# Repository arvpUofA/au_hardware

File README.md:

# au_hardware #

Welcome to ARVP's hardware design repository.

In here you can find all of our electrical designs.

### Github Guides
- http://rogerdudler.github.io/git-guide/ 
- Intro to GitHub with Hello World
- https://www.youtube.com/watch?v=0fKg7e37bQE 

## Branches
- master -  contains boards that have been fabricated, soldered, tested and are part of this year’s robot
- develop - contains boards that have been designed, approved, and the fab company has accepted their designs.
- project_branch - every new project is branched from develop. Naming convention of branch is as follows:

All names in lowercase and can only include alphanumeric characters and underscores.
The naming format will be `project_board` (e.g. `motor_breakout` or `power_main`)
If the project only contains one board (e.g. `killswitch`) then naming format will be `project`.
If this is a newer iteration of the same board create a branch with the version number `project_board_vx` (where `x` is the version number).

## Starting a new project

```
    # Clone the develop branch of the repository
    git clone -b develop https://github.com/arvpUofA/au_hardware 
    # Create a new branch from develop
    git checkout -b project_board   
    # Push the branch to remote
    git push -u origin project_board
```

Create folder structure for project as follows:
Inside the `au_hardware`/`project_board` branch, create the project folder if it does not exist. (e.g. `motor`, `power`, etc)
Inside the project folder create a board folder if it does not exist. If this is a different version of the same board, don’t create a new folder. Use the same folder as before. If the project contains only one board, you don’t need to create this folder.
Naming of the folder will follow the same conventions as branch naming conventions (no spaces please). 
Add required files to this folder. Make sure to commit and push periodically.

## Project requirements
Once the board design is complete, run the following:

- ERC on schematic - error checking for schematic
- DRC on board - design rule check for pcb. (e.g. drc/JLCPCB2Layer.drc file)
- Generate image files for schematic and pcb. Make sure the images are clear with at least 200dpi.
- Generate CAM files.
- Test CAM files using a CAM Viewer (e.g. View Mate or Gerbv)

Each project needs the following files:
- [ ] project_board.sch - schematic file for project
- [ ] project_board.brd - board file for project
- [ ] project_board_sch.png - image of schematic
- [ ] project_board_brd.png - image of pcb
- [ ] project_board/ - this folder contains all the CAM files
- [ ] project_board.zip - ZIP of the CAM folder

## Pull request and close

Once all requirements have been complete, create a pull request to merge this branch into develop

Set base: `develop` and compare: `your_branch`. Click "Create pull request".
 
Set the PR name, create a detailed description, and assign the team lead to review your pull request.   
The reviewer will check your design, and rerun ERC and DRC.

If the reviewer has any suggestions, implement them in your design, regenerate all required files and commit and push everything.

After the review is complete, the board will be uploaded to the fabrication website. If they approve the design, the reviewer will merge and close the pull request. Make sure you don’t continue work on this closed branch.
A new release tag will also be created for the board with format boardname[version]. E.g. killswitch1.0. At any point you can look at any older version by going to that specific tag.
Note that, if during reviews we discovered any changes we want to make in the next version, we will put these as issues on the repository and assign them to you. These need to be fixed in the next version before you make a PR.

## Starting a new revision

Once your PRs have been closed a.k.a the board has been sent out, the branch you were working on will be deleted, and you will need to make
a new branch off `develop` with the latest version number for that board.

```
    # To start switch to develop
    git checkout develop
    # Pull the latest version of the code
    git pull 
```

Create a new branch for the next iteration of the board. The naming format for the branch is `boardname_vx`

```
    # Example for V2 of comm_hub
    git checkout -b comm_hub_v2
```

Find the appropriate project folder where the current board revision is saved (e.g.  communications_hub) and create a new folder within this project folder with the new version number (e.g. communications_hub\communications_hub_v2).
Make sure to push your new branch to github using 

```
git push -u origin name_of_new_branch
```

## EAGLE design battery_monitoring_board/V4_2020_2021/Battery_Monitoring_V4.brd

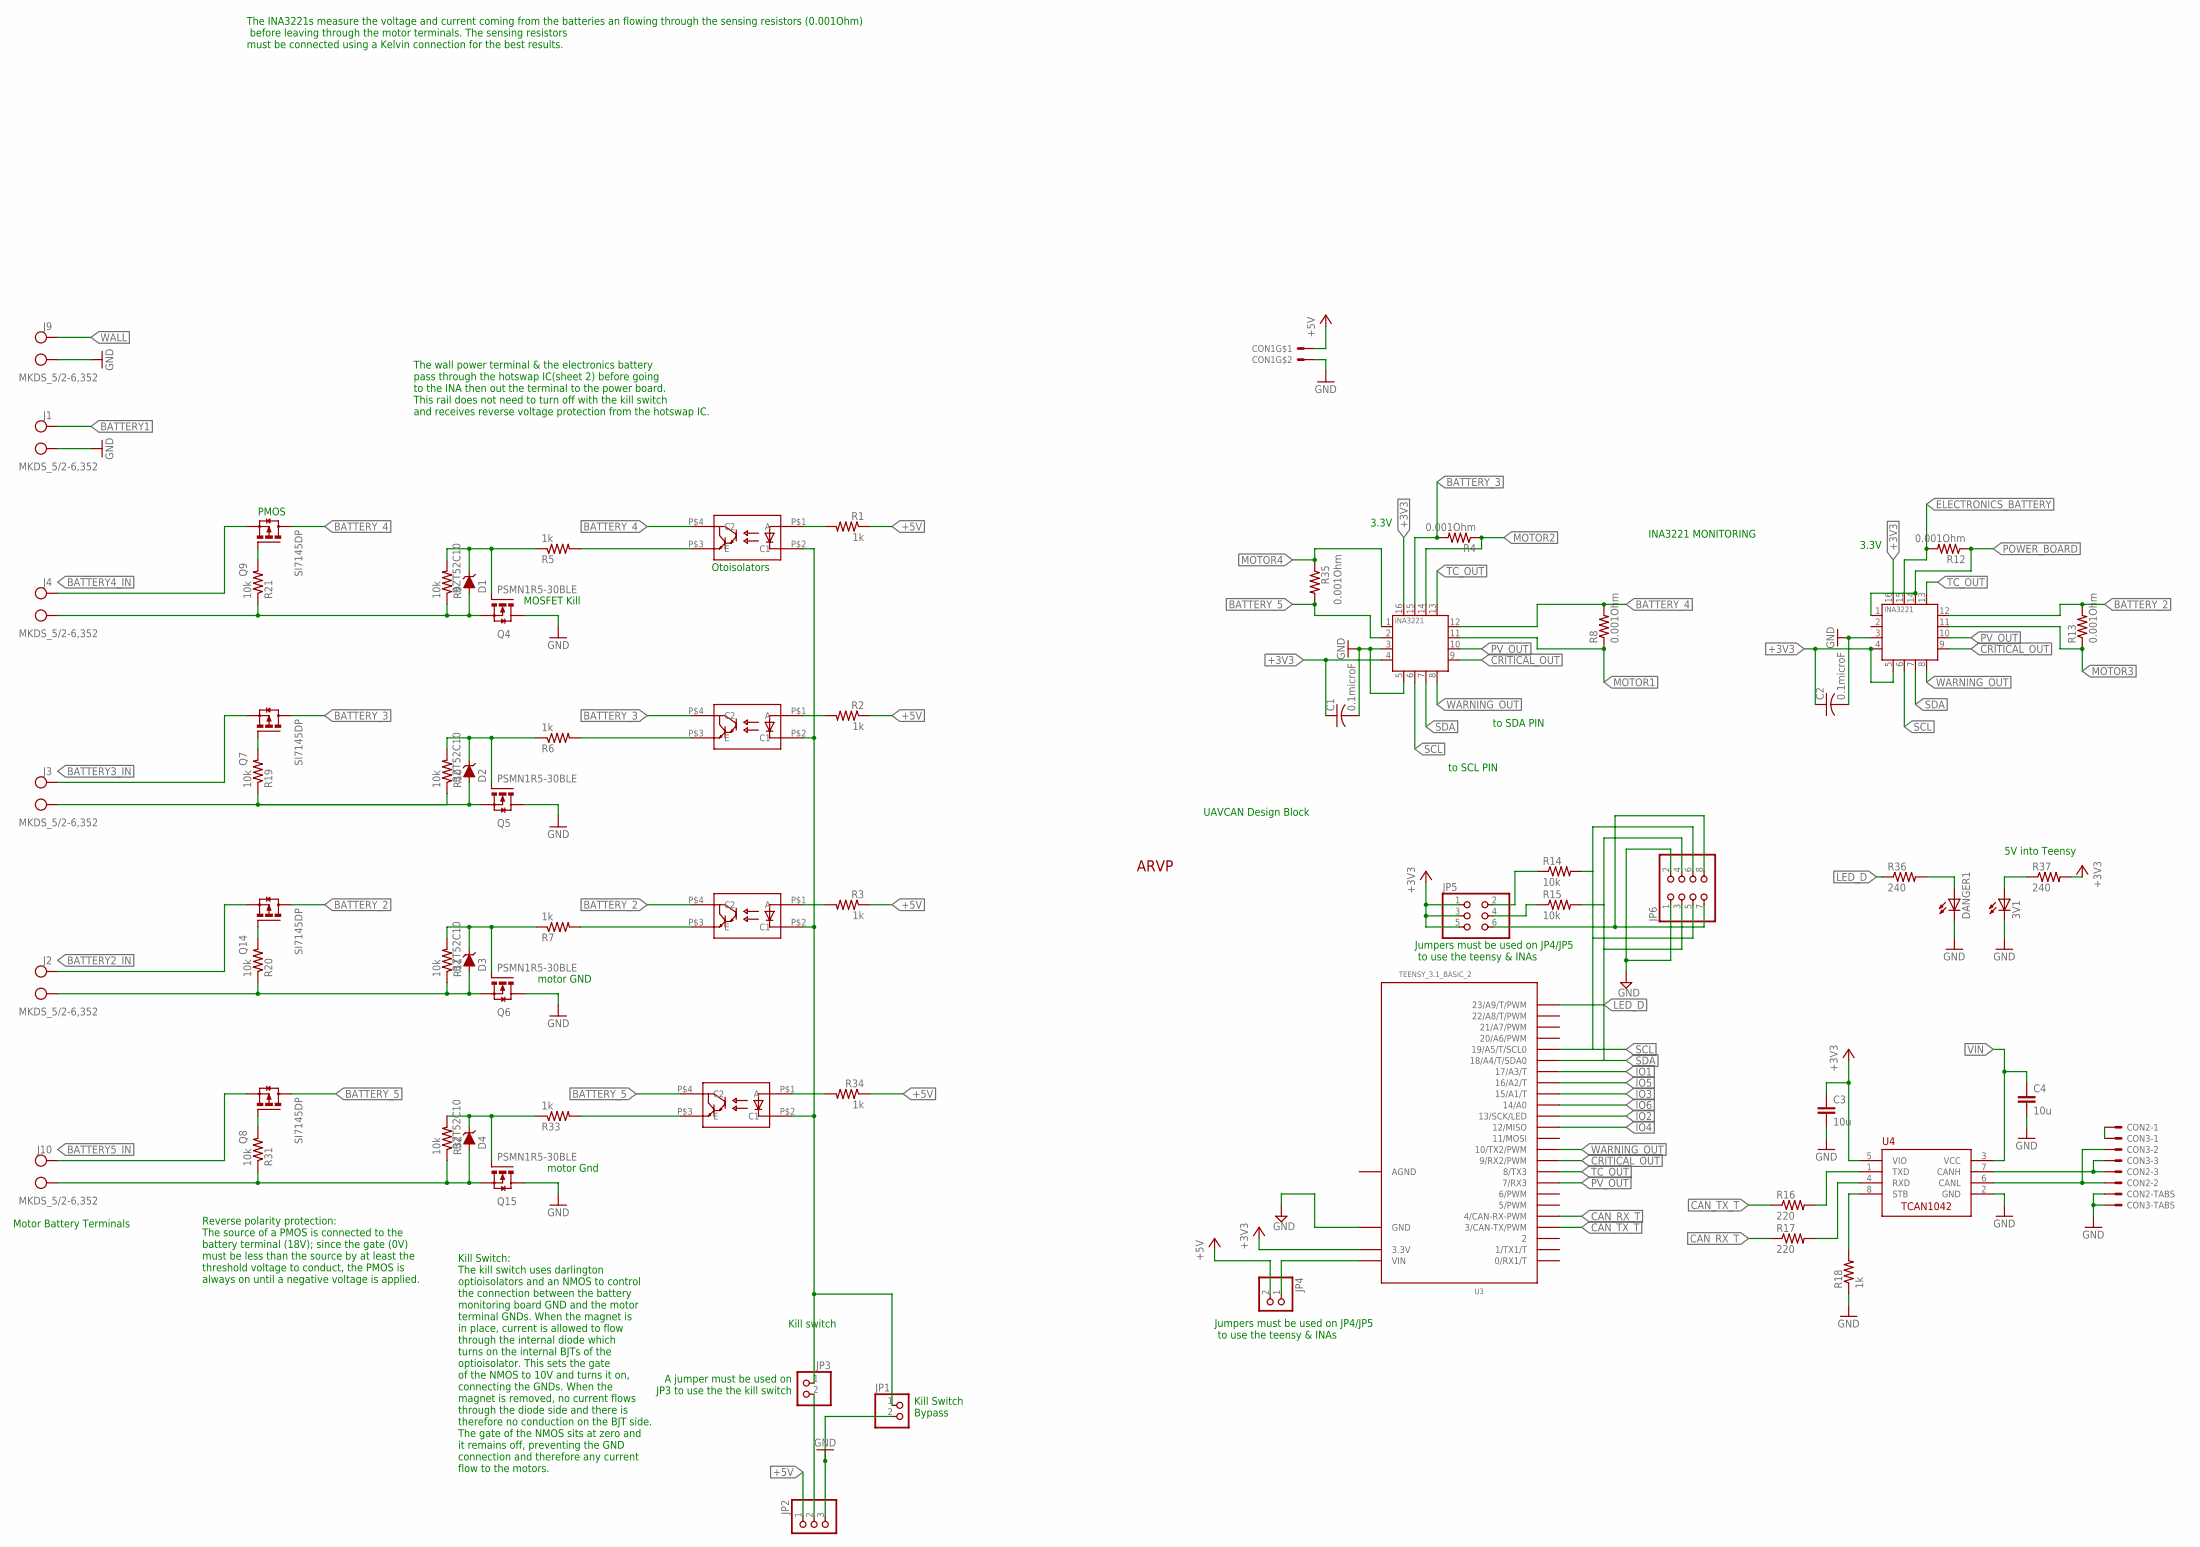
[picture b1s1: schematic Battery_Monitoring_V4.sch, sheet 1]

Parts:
3V1: LEDSMT1206; 1206
ARVP1: ARVP_LOGO; ARVP
C1, C2: 0.1microF; C2012
C3, C4: 10u; C0805
CON1: MOLEX_5566-2; 5566-2
CON2, CON3: SM03B-GHS-TB
D1, D2, D3, D4: BZT52C10; SOD-123
DANGER1: LEDSMT1206; 1206
J1, J2, J3, J4, J9, J10: MKDS_5/2-6,352; MKDS_5/2-6,35
JP1, JP3, JP4: PINHD-1X2; 1X02
JP2: PINHD-1X3; 1X03
JP5: PINHD-2X3; 2X03
JP6: PINHD-2X4; 2X04
Q1, Q2, Q3, Q16: TCLD1000CT; SOP-4L
Q4, Q5, Q6, Q15: PSMN1R5-30BLE; SOT404/D2PAK
Q7, Q8, Q9, Q14: SI7145DP; SO-8/PPAK/TEST; MPN SI7145DP-T1-GE3
R1, R2, R3, R18, R34: 1k; R0805
R4, R8, R12, R13, R35: 0.001Ohm; 3920
R5, R6, R7, R33: 1k; M1206
R9, R10, R11, R32: 10k; M1206
R14, R15: 10k; R1206
R16, R17: 220; R0805
R19, R20, R21, R31: 10k; M1206; MPN RC0603FR-0710KL
R36, R37: 240; R1206
U1, U2: INA3221.; HVQFN16_4X4
U3: TEENSY_3.1_BASIC_2
U4: TCAN1042HVDR; SO-8

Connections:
+3V3: C1.1, C2.1, C3.1, JP5.1, JP5.3, JP5.5, R37.2, U1.4 (VS), U1.16 (VPU), U2.4 (VS), U2.5 (A0), U2.16 (VPU), U3.3.3V, U4.5 (VIO)
+5V: CON1.1, JP2.1, JP4.2, R1.1, R2.1, R3.1, R34.1; also elsewhere on the board
AGND: U3.AGND
BATT1GND: D1.P$2 (A), J4.1 (KL), Q4.3S (S), R9.1, R21.1
BATT2GND: D2.P$2 (A), J3.1 (KL), Q5.3S (S), R10.1, R19.1
BATT3GND: D3.P$2 (A), J2.1 (KL), Q6.3S (S), R11.1, R20.1
BATT5GND: D4.P$2 (A), J10.1 (KL), Q15.3S (S), R31.1, R32.1
BATTERY1: J1.2 (KL1); also elsewhere on the board
BATTERY2_IN: J2.2 (KL1), Q14.S@1 (S), Q14.S@2 (S), Q14.S@3 (S)
BATTERY3_IN: J3.2 (KL1), Q7.S@1 (S), Q7.S@2 (S), Q7.S@3 (S)
BATTERY4_IN: J4.2 (KL1), Q9.S@1 (S), Q9.S@2 (S), Q9.S@3 (S)
BATTERY5_IN: J10.2 (KL1), Q8.S@1 (S), Q8.S@2 (S), Q8.S@3 (S)
BATTERY_2: Q3.P$4 (C2), Q14.D@1 (D), Q14.D@2 (D), Q14.D@3 (D), Q14.D@4 (D), Q14.D@5 (D), R13.P$2 (2), U2.12 (IN+1)
BATTERY_3: Q2.P$4 (C2), Q7.D@1 (D), Q7.D@2 (D), Q7.D@3 (D), Q7.D@4 (D), Q7.D@5 (D), R4.P$2 (2), U1.15 (IN+2)
BATTERY_4: Q1.P$4 (C2), Q9.D@1 (D), Q9.D@2 (D), Q9.D@3 (D), Q9.D@4 (D), Q9.D@5 (D), R8.P$2 (2), U1.12 (IN+1)
BATTERY_5: Q8.D@1 (D), Q8.D@2 (D), Q8.D@3 (D), Q8.D@4 (D), Q8.D@5 (D), Q16.P$4 (C2), R35.P$2 (2), U1.2 (IN+3)
CANH1: CON2.P$3, CON3.P$3, U4.7 (CANH)
CANL1: CON2.P$2, CON3.P$2, U4.6 (CANL)
CANSH1: CON2.P$1, CON3.P$1
CAN_RX1: R17.2, U4.4 (RXD)
CAN_RX_T: R17.1, U3.4 (4/CAN-RX-PWM)
CAN_TX2: R16.2, U4.1 (TXD)
CAN_TX_T: R16.1, U3.3 (3/CAN-TX/PWM)
CRITICAL_OUT: U1.9 (CRITICAL), U2.9 (CRITICAL), U3.9 (9/RX2/PWM)
E1: Q1.P$3 (E), R5.2
E2: Q2.P$3 (E), R6.2
E3: Q3.P$3 (E), R7.2
ELECTRONICS_BATTERY: R12.P$2 (2), U2.15 (IN+2); also elsewhere on the board
GND: 3V1.C, C1.2, C2.2, C3.2, C4.2, CON1.2, CON2.P$4, CON2.P$5, CON3.P$4, CON3.P$5, DANGER1.C, J1.1 (KL), J9.1 (KL), JP1.2, JP2.3, JP6.1, JP6.2, Q4.2D (D), Q5.2D (D), Q6.2D (D), Q15.2D (D), R18.1, U1.3 (GND), U1.5 (A0), U2.3 (GND), U3.GND, U4.2 (GND); also elsewhere on the board
I2C_3V1: JP5.6, JP6.7, JP6.8
IO1: U3.17/A3 (17/A3/T); also elsewhere on the board
IO2: U3.13 (13/SCK/LED); also elsewhere on the board
IO3: U3.15/A1 (15/A1/T); also elsewhere on the board
IO4: U3.12 (12/MISO); also elsewhere on the board
IO5: U3.16/A2 (16/A2/T); also elsewhere on the board
IO6: U3.14/A0; also elsewhere on the board
LED_D: R36.1, U3.23/A9 (23/A9/T/PWM)
MG1: D1.P$1 (C), Q4.1G (G), R5.1, R9.2
MG2: D2.P$1 (C), Q5.1G (G), R6.1, R10.2
MG3: D3.P$1 (C), Q6.1G (G), R7.1, R11.2
MG4: D4.P$1 (C), Q15.1G (G), R32.2, R33.1
MOTOR1: R8.P$1 (1), U1.11 (IN-1); also elsewhere on the board
MOTOR2: R4.P$1 (1), U1.14 (IN-2); also elsewhere on the board
MOTOR3: R13.P$1 (1), U2.11 (IN-1); also elsewhere on the board
MOTOR4: R35.P$1 (1), U1.1 (IN-3); also elsewhere on the board
unnamed: Q1.P$1 (A), R1.2
unnamed: Q2.P$1 (A), R2.2
unnamed: Q3.P$1 (A), R3.2
unnamed: JP1.1, JP3.1, Q1.P$2 (C1), Q2.P$2 (C1), Q3.P$2 (C1), Q16.P$2 (C1)
unnamed: JP2.2, JP3.2
unnamed: Q7.G, R19.2
unnamed: Q14.G, R20.2
unnamed: Q9.G, R21.2
unnamed: Q8.G, R31.2
unnamed: Q16.P$3 (E), R33.2
unnamed: Q16.P$1 (A), R34.2
unnamed: 3V1.A, R37.1
unnamed: DANGER1.A, R36.2
POWER_BOARD: R12.P$1 (1), U2.1 (IN-3), U2.14 (IN-2); also elsewhere on the board
PV_OUT: U1.10 (PV), U2.10 (PV), U3.7 (7/RX3)
SCL: JP6.5, JP6.6, R14.2, U1.6 (SCL), U2.6 (SCL), U3.19/A5 (19/A5/T/SCL0)
SCL_3V1: JP5.2, R14.1
SDA: JP6.3, JP6.4, R15.2, U1.7 (SDA), U2.7 (SDA), U3.18/A4 (18/A4/T/SDA0)
SDA_3V1: JP5.4, R15.1
STB1: R18.2, U4.8 (STB)
TC_OUT: U1.13 (TC), U2.13 (TC), U3.8 (8/TX3)
VIN: C4.1, JP4.1, U3.VIN, U4.3 (VCC)
WALL: J9.2 (KL1); also elsewhere on the board
WARNING_OUT: U1.8 (WARNING), U2.8 (WARNING), U3.10 (10/TX2/PWM)

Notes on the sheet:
3.3V
Kill switch
motor GND
INA3221 MONITORING
Otoisolators
MOSFET Kill
to SDA PIN
to SCL PIN
A jumper must be used on JP3 to use the the kill switch
Kill Switch Bypass
PMOS
The wall power terminal & the electronics battery pass through the hotswap IC(sheet 2) before going to the INA then out the terminal to the power board. This rail does not need to turn off with the kill switch and receives reverse voltage protection from the hotswap IC.
The INA3221s measure the voltage and current coming from the batteries an flowing through the sensing resistors (0.001Ohm) before leaving through the motor terminals. The sensing resistors must be connected using a Kelvin connection for the best results.
Jumpers must be used on JP4/JP5 to use the teensy & INAs
Reverse polarity protection: The source of a PMOS is connected to the battery terminal (18V); since the gate (0V) must be less than the source by at least the threshold voltage to conduct, the PMOS is always on until a negative voltage is applied.
Kill Switch: The kill switch uses darlington optioisolators and an NMOS to control the connection between the battery monitoring board GND and the motor terminal GNDs. When the magnet is in place, current is allowed to flow through the internal diode which turns on the internal BJTs of the optioiso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
UAVCAN Design Block
Motor Battery Terminals
motor Gnd
5V into Teensy

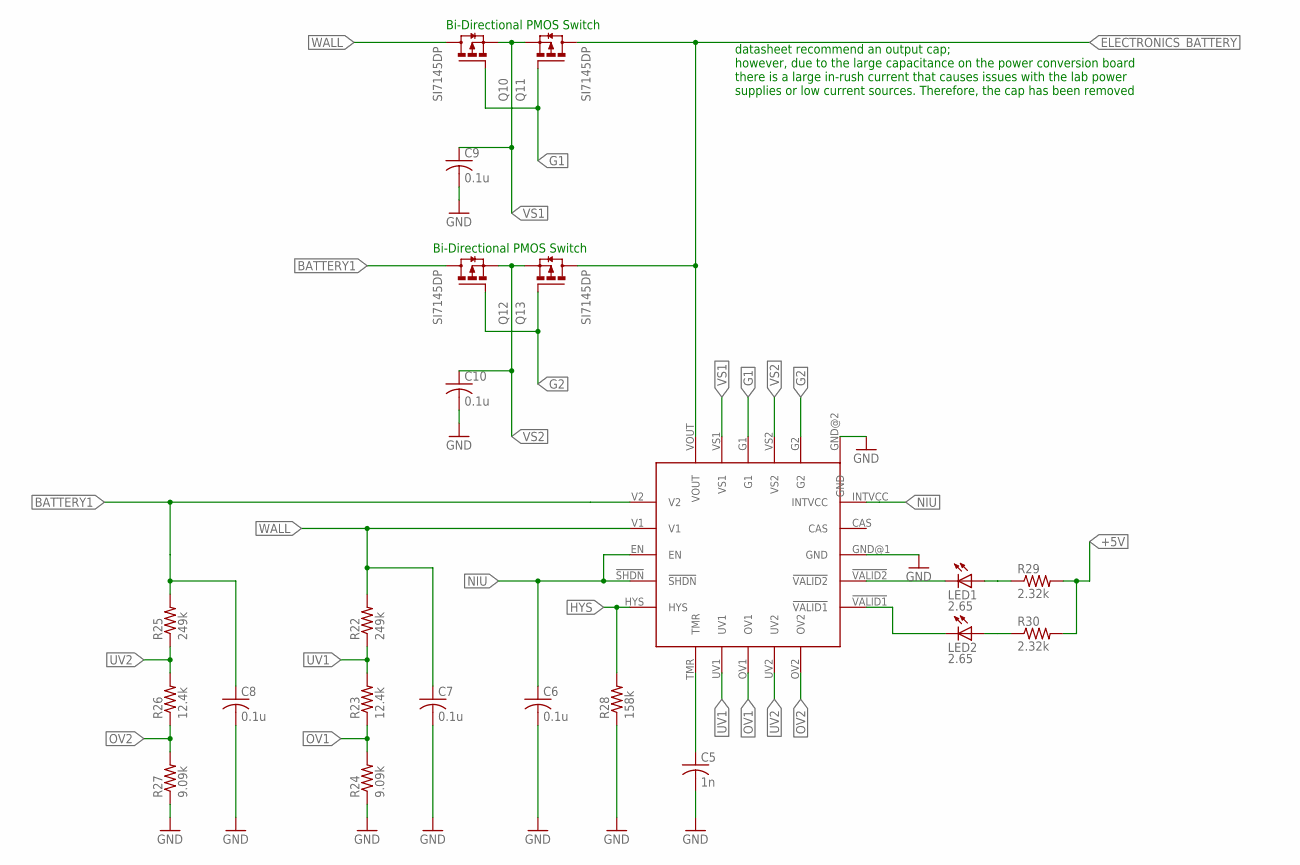
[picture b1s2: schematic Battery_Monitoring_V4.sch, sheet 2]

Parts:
C5: 1n; C0805
C6, C7, C8, C9, C10: 0.1u; C0805
LED1, LED2: 2.65; SML0805
Q10, Q11, Q12, Q13: SI7145DP; SO-8/PPAK/TEST
R22, R25: 249k; R1206
R23, R26: 12.4k; R0805
R24, R27: 9.09k; R0805
R28: 158k; R0805
R29, R30: 2.32k; R0805
U5: LTC4418; 20-QFN(4X4)

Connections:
!VALID1: LED2.C, U5.!VALID1
!VALID2: LED1.C, U5.!VALID2
+5V: R29.2, R30.2; also elsewhere on the board
BATTERY1: C8.1, Q12.D@1 (D), Q12.D@2 (D), Q12.D@3 (D), Q12.D@4 (D), Q12.D@5 (D), R25.2, U5.V2; also elsewhere on the board
ELECTRONICS_BATTERY: Q11.D@1 (D), Q11.D@2 (D), Q11.D@3 (D), Q11.D@4 (D), Q11.D@5 (D), Q13.D@1 (D), Q13.D@2 (D), Q13.D@3 (D), Q13.D@4 (D), Q13.D@5 (D), U5.VOUT; also elsewhere on the board
G1: Q10.G, Q11.G, U5.G1
G2: Q12.G, Q13.G, U5.G2
GND: C5.2, C6.2, C7.2, C8.2, C9.2, C10.2, R24.1, R27.1, R28.1, U5.GND@1 (GND), U5.GND@2 (GND); also elsewhere on the board
HYS: R28.2, U5.HYS
unnamed: LED1.A, R29.1
unnamed: LED2.A, R30.1
unnamed: C5.1, U5.TMR
NIU: C6.1, U5.!SHDN, U5.EN, U5.INTVCC
OV1: R23.1, R24.2, U5.OV1
OV2: R26.1, R27.2, U5.OV2
UV1: R22.1, R23.2, U5.UV1
UV2: R25.1, R26.2, U5.UV2
VS1: C9.1, Q10.S@1 (S), Q10.S@2 (S), Q10.S@3 (S), Q11.S@1 (S), Q11.S@2 (S), Q11.S@3 (S), U5.VS1
VS2: C10.1, Q12.S@1 (S), Q12.S@2 (S), Q12.S@3 (S), Q13.S@1 (S), Q13.S@2 (S), Q13.S@3 (S), U5.VS2
WALL: C7.1, Q10.D@1 (D), Q10.D@2 (D), Q10.D@3 (D), Q10.D@4 (D), Q10.D@5 (D), R22.2, U5.V1; also elsewhere on the board

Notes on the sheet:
Bi-Directional PMOS Switch
datasheet recommend an output cap; however, due to the large capacitance on the power conversion board there is a large in-rush current that causes issues with the lab power supplies or low current sources. Therefore, the cap has been removed

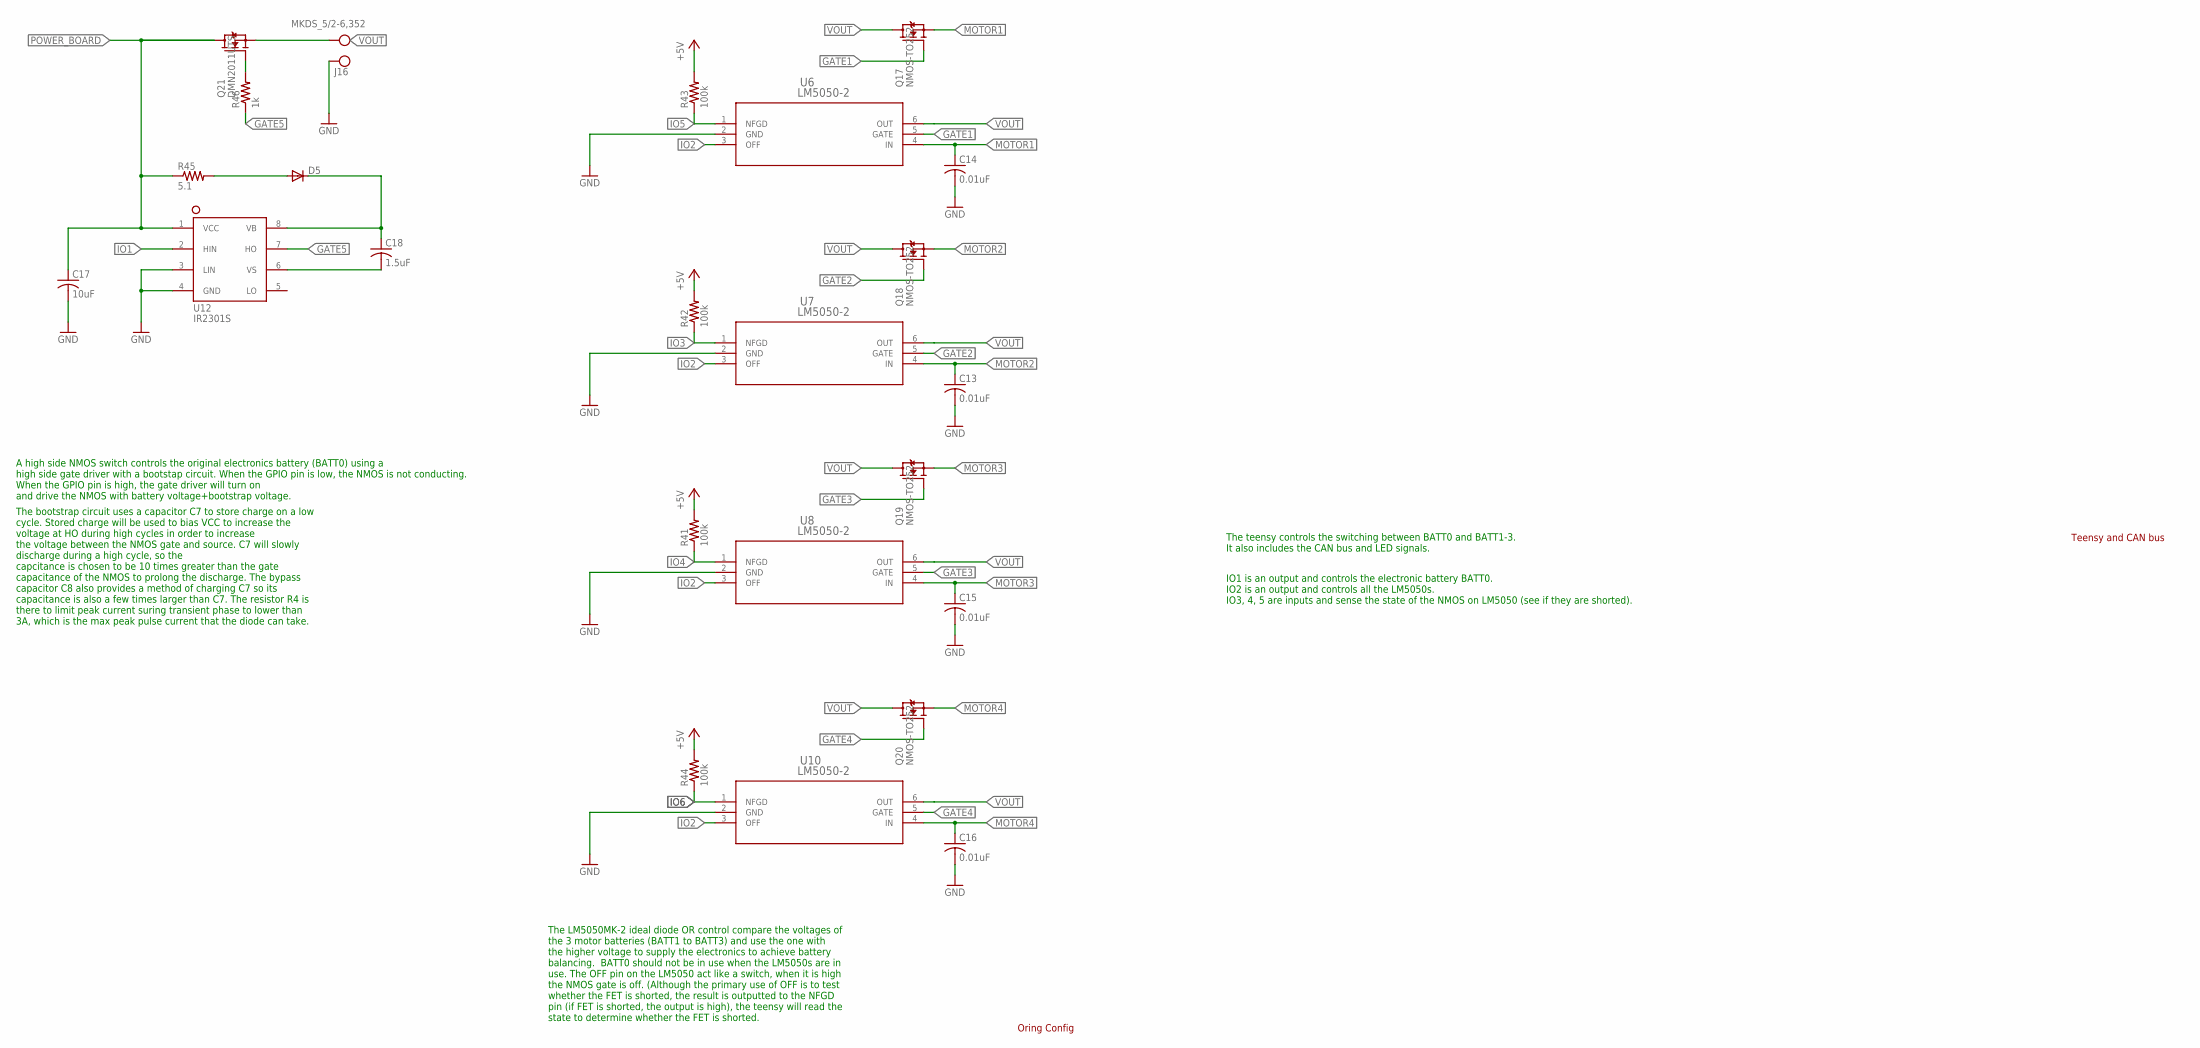
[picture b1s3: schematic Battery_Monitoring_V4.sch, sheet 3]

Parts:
C13, C14, C15, C16: 0.01uF; C0805
C17: 10uF; C1206
C18: 1.5uF; C0805
D5: DIODE-DO-214AC; DO-214AC
J16: MKDS_5/2-6,352; MKDS_5/2-6,35
Q17, Q18, Q19, Q20: NMOS-TO252; TO252
Q21: DMN2011UTS; SOP65P640X120-8N
R41, R42, R43, R44: 100k; R1206
R45: 5.1; R1206
R46: 1k; R0805
U6, U7, U8, U10: LM5050-2; MK06A
U12: IR2301S; SOIC8

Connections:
+5V: R41.2, R42.2, R43.2, R44.2; also elsewhere on the board
GATE1: Q17.1 (G), U6.5 (GATE)
GATE2: Q18.1 (G), U7.5 (GATE)
GATE3: Q19.1 (G), U8.5 (GATE)
GATE4: Q20.1 (G), U10.5 (GATE)
GATE5: R46.1, U12.7 (HO)
GND: C13.2, C14.2, C15.2, C16.2, C17.2, J16.2 (KL1), U6.2 (GND), U7.2 (GND), U8.2 (GND), U10.2 (GND), U12.3 (LIN), U12.4 (GND); also elsewhere on the board
IO1: U12.2 (HIN); also elsewhere on the board
IO2: U6.3 (OFF), U7.3 (OFF), U8.3 (OFF), U10.3 (OFF); also elsewhere on the board
IO3: R42.1, U7.1 (NFGD); also elsewhere on the board
IO4: R41.1, U8.1 (NFGD); also elsewhere on the board
IO5: R43.1, U6.1 (NFGD); also elsewhere on the board
IO6: R44.1, U10.1 (NFGD); also elsewhere on the board
MOTOR1: C14.1, Q17.3 (S), U6.4 (IN); also elsewhere on the board
MOTOR2: C13.1, Q18.3 (S), U7.4 (IN); also elsewhere on the board
MOTOR3: C15.1, Q19.3 (S), U8.4 (IN); also elsewhere on the board
MOTOR4: C16.1, Q20.3 (S), U10.4 (IN); also elsewhere on the board
unnamed: C18.2, U12.6 (VS)
unnamed: C18.1, D5.C, U12.8 (VB)
unnamed: Q21.4 (G), R46.2
unnamed: D5.A, R45.2
POWER_BOARD: C17.1, Q21.5 (D), Q21.6 (D), Q21.7 (D), Q21.8 (D), R45.1, U12.1 (VCC); also elsewhere on the board
VOUT: J16.1 (KL), Q17.2 (D), Q18.2 (D), Q19.2 (D), Q20.2 (D), Q21.1 (S), Q21.2 (S), Q21.3 (S), U6.6 (OUT), U7.6 (OUT), U8.6 (OUT), U10.6 (OUT)

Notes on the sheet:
Teensy and CAN bus
Oring Config
A high side NMOS switch controls the original electronics battery (BATT0) using a high side gate driver with a bootstap circuit. When the GPIO pin is low, the NMOS is not conducting. When the GPIO pin is high, the gate driver will turn on and drive the NMOS with battery voltage+bootstrap voltage.
The LM5050MK-2 ideal diode OR control compare the voltages of the 3 motor batteries (BATT1 to BATT3) and use the one with the higher voltage to supply the electronics to achieve battery balancing. BATT0 should not be in use when the LM5050s are in use. The OFF pin on the LM5050 act like a switch, w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
The teensy controls the switching between BATT0 and BATT1-3. It also includes the CAN bus and LED signals.
IO1 is an output and controls the electronic battery BATT0. IO2 is an output and controls all the LM5050s. IO3, 4, 5 are inputs and sense the state of the NMOS on LM5050 (see if they are shorted).
The bootstrap circuit uses a capacitor C7 to store charge on a low cycle. Stored charge will be used to bias VCC to increase the voltage at HO during high cycles in order to increase the voltage between the NMOS gate and source. C7 will slowly discharge during a high cycle, so the capcitance is cho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

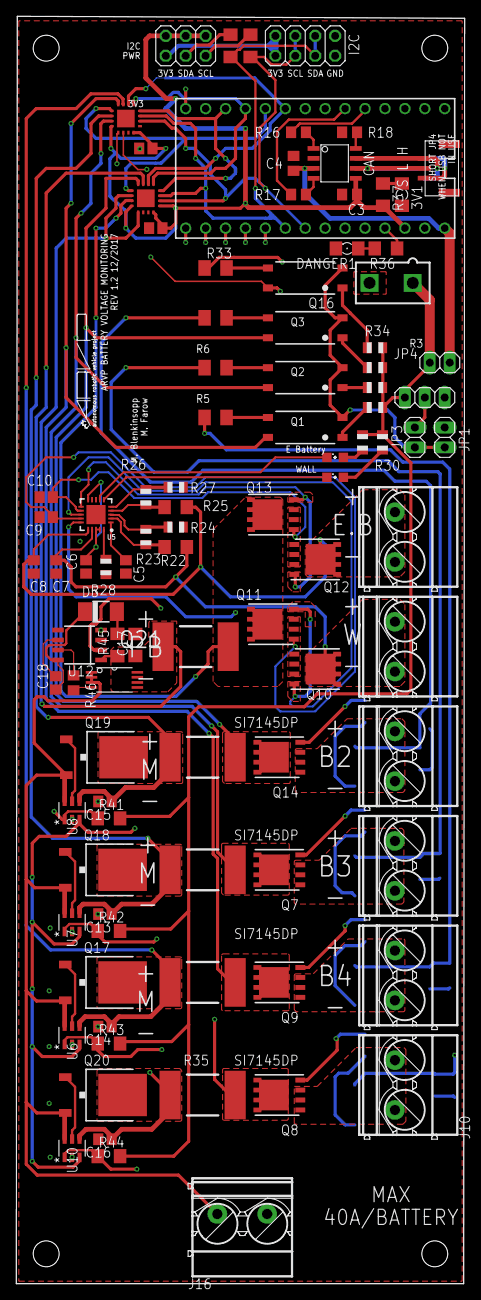
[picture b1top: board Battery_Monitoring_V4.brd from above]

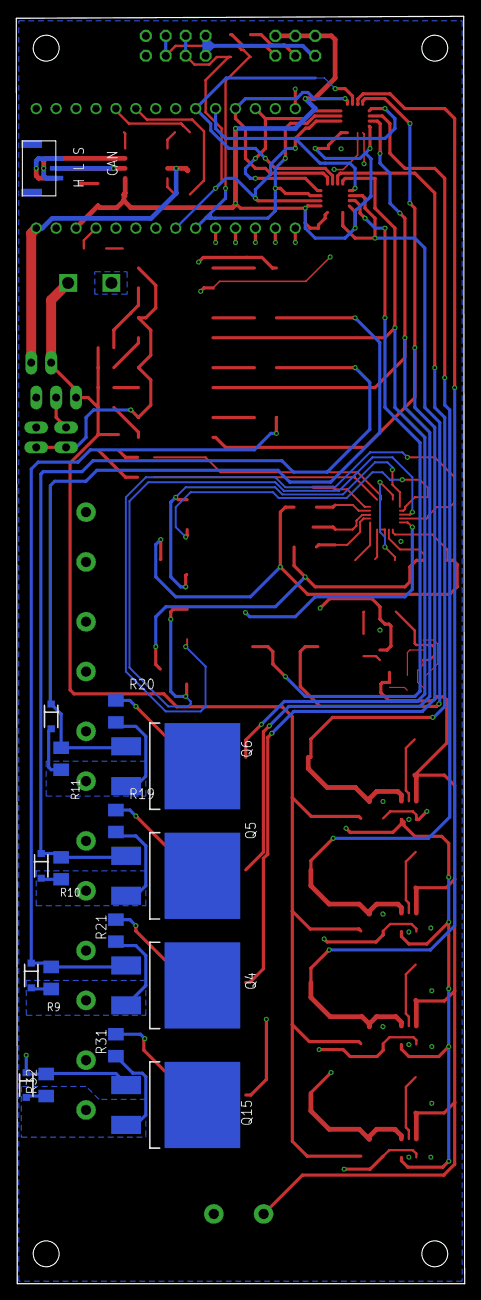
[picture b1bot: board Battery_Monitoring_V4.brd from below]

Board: 4 copper layers, 57.1 x 161.5 mm, 120 parts (17 on the bottom side), 93 nets.

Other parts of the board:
U$18, U$24, U$25, U$26: STAND-OFF

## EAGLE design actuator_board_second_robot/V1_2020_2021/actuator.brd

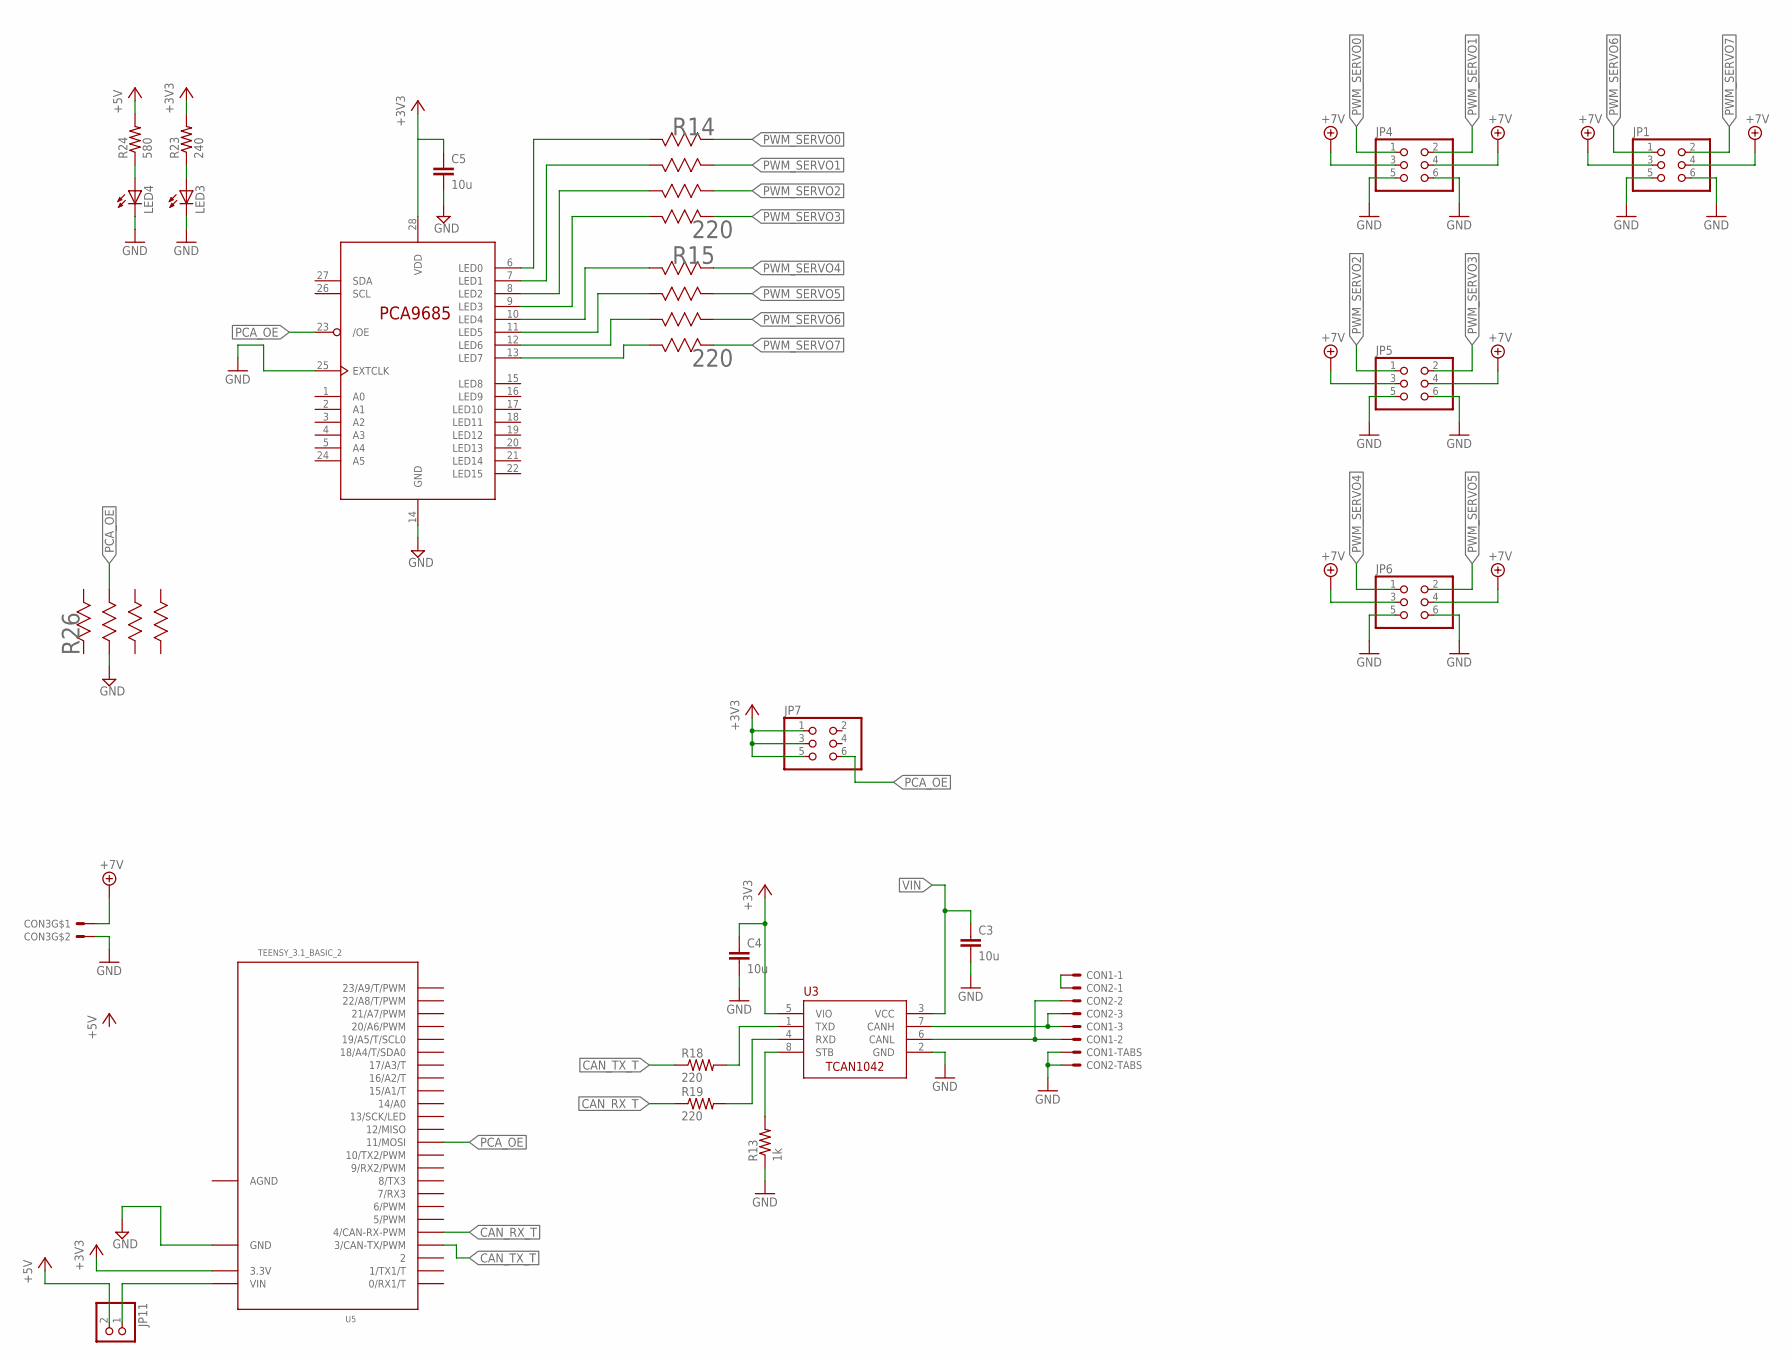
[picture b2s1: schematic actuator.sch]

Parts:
C3, C4, C5: 10u; C0805
CON1, CON2: SM03B-GHS-TB
CON3: MOLEX_5566-2; 5566-2
JP1, JP4, JP5, JP6, JP7: PINHD-2X3; 2X03
JP11: PINHD-1X2; 1X02
LED3, LED4: LEDCHIPLED_1206; CHIPLED_1206
R13: 1k; R0805
R14, R15: 220; EXBV8V-M
R18, R19: 220; R0805
R23: 240; R1206
R24: 580; R1206
R26: 10k; EXBV8V-M
U3: TCAN1042HVDR; SO-8
U4: PCA9685PW; TSSOP28
U5: TEENSY_3.1_BASIC_2

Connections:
+3V3: C4.1, C5.1, JP7.1, JP7.3, JP7.5, R23.2, U3.5 (VIO), U4.28 (VDD), U5.3.3V
+5V: JP11.2, R24.2
+7V: CON3.1, JP1.3, JP1.4, JP4.3, JP4.4, JP5.3, JP5.4, JP6.3, JP6.4
AGND: U5.AGND
CANH: CON1.P$3, CON2.P$3, U3.7 (CANH)
CANL: CON1.P$2, CON2.P$2, U3.6 (CANL)
CANSH: CON1.P$1, CON2.P$1
CAN_RX: R19.2, U3.4 (RXD)
CAN_RX_T: R19.1, U5.4 (4/CAN-RX-PWM)
CAN_TX1: R18.2, U3.1 (TXD)
CAN_TX_T: R18.1, U5.3 (3/CAN-TX/PWM)
GND: C3.2, C4.2, C5.2, CON1.P$4, CON1.P$5, CON2.P$4, CON2.P$5, CON3.2, JP1.5, JP1.6, JP4.5, JP4.6, JP5.5, JP5.6, JP6.5, JP6.6, LED3.C, LED4.C, R13.1, R26.2 (23), U3.2 (GND), U4.14 (GND), U4.25 (EXTCLK), U5.GND
unnamed: LED3.A, R23.1
unnamed: LED4.A, R24.1
PCA_OE: JP7.6, R26.7 (74), U4.23 (/OE), U5.11 (11/MOSI)
PWM_CH0: R14.8 (82), U4.6 (LED0)
PWM_CH1: R14.7 (74), U4.7 (LED1)
PWM_CH2: R14.6 (66), U4.8 (LED2)
PWM_CH3: R14.5 (58), U4.9 (LED3)
PWM_CH4: R15.8 (82), U4.10 (LED4)
PWM_CH5: R15.7 (74), U4.11 (LED5)
PWM_CH6: R15.6 (66), U4.12 (LED6)
PWM_CH7: R15.5 (58), U4.13 (LED7)
PWM_SERVO0: JP4.1, R14.1 (11)
PWM_SERVO1: JP4.2, R14.2 (23)
PWM_SERVO2: JP5.1, R14.3 (35)
PWM_SERVO3: JP5.2, R14.4 (47)
PWM_SERVO4: JP6.1, R15.1 (11)
PWM_SERVO5: JP6.2, R15.2 (23)
PWM_SERVO6: JP1.1, R15.3 (35)
PWM_SERVO7: JP1.2, R15.4 (47)
STB: R13.2, U3.8 (STB)
VIN: C3.1, JP11.1, U3.3 (VCC), U5.VIN

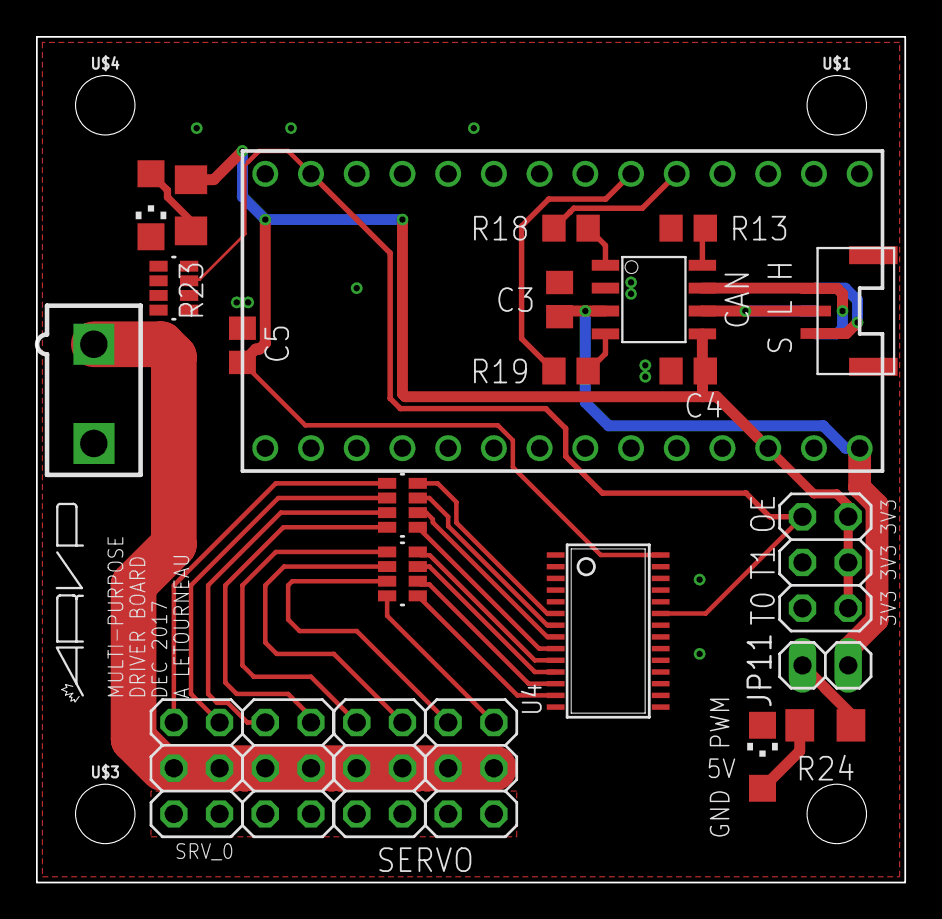
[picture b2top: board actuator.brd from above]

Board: 2 copper layers, 48.3 x 47.0 mm, 32 parts (1 on the bottom side), 32 nets.

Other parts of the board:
U$1, U$3, U$4, U$8: STAND-OFF
U$5: LOGO3
U$6: LETTER_L
U$7: DOCFIELD

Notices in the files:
parts and their libraries:
SparkFun-Hardware: Licensing: Creative Commons ShareAlike 4.0 International - https://creativecommons.org/licenses/by-sa/4.0
SparkFun-Sensors: Licensing: CC v3.0 Share-Alike You are welcome to use this library for commercial purposes.
Kondensatoren: Copyright: Würth Elektronik
